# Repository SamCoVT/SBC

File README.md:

# SBC
SamCo's Single Board Computer (65C02)

This single board computer was constructed for fun.  It has the
following specifications:

* 65C02 processor
* 32K RAM (with 256 addresses reserved for I/O)
* 32K ROM 
* 65C22 Versatile Interface Adapter (VIA)
* 65C51 Asynchronous Communications Interface Adapter (ACIA)
* 2x16 LCD
* Support for USB or external 5V power

After trying out writing programs in assembly and in BASIC, I found
the [Tali Forth 2](https://github.com/scotws/TaliForth2) project, and
that's what I've been using as an operating system/programming
language ever since.

## Memory Map

The memory map is currently as follows:

|Memory Range | Function|
|-------------|--------|
|$0000-$7EFF  | RAM|
|$7F00-$7F3F  | VIA (65C22 - parallel I/O)|
|$7F40-$7F7F  | EXSEL1 (External Select #1) (Active Low)|
|$7F80-$7FBF  | ACIA (65C51 - Serial port)|
|$7FC0-$7FFF  | LCD|

The EXSEL1 line is brought out to the expansion bus on the righ
side of the PCB and is available for use.  The EXSEL2 line is an
active-high version of the /RESET signal.  Both of these signals are
not currently used by the SBC and can be repurposed by reprogramming
the GAL.

The memory decoding is handled by a GAL22V10, programmed from the
ADDECODE.PLD file.  I used Wincupl (run under Wine on Linux) to
generate the .jed (JEDEC) file, and then I used Galblast on an old
Windows 98 machine with a parallel port adapter to program the GAL.

## Errata

* Because I used a WDC65C22S (which has a totem-pole IRQ output rather
  than the WDC65C22N which has an open drain IRQ output,) I had to cut
  the IRQ trace and add a Schottky diode (cathode towards pin 21 of
  IC6) across the gap.

* I needed to add approximately 30pF of capacitance to the ACIA
  crystal to get it to start up and oscillate reliably.  No provision
  was made on the board for this, so I added it on the back side of
  the board between pins 1 and 6.  I also needed to add a 1Meg Ohm
  resistor across the crystal pins when using an RCA CDP65C51 (but did
  not need this when using a Rockwell part.)

# License
The Eagle schematic board files are provided here under a Creative
Commons BY-SA 2.0 (CC BY-SA 2.0) license.

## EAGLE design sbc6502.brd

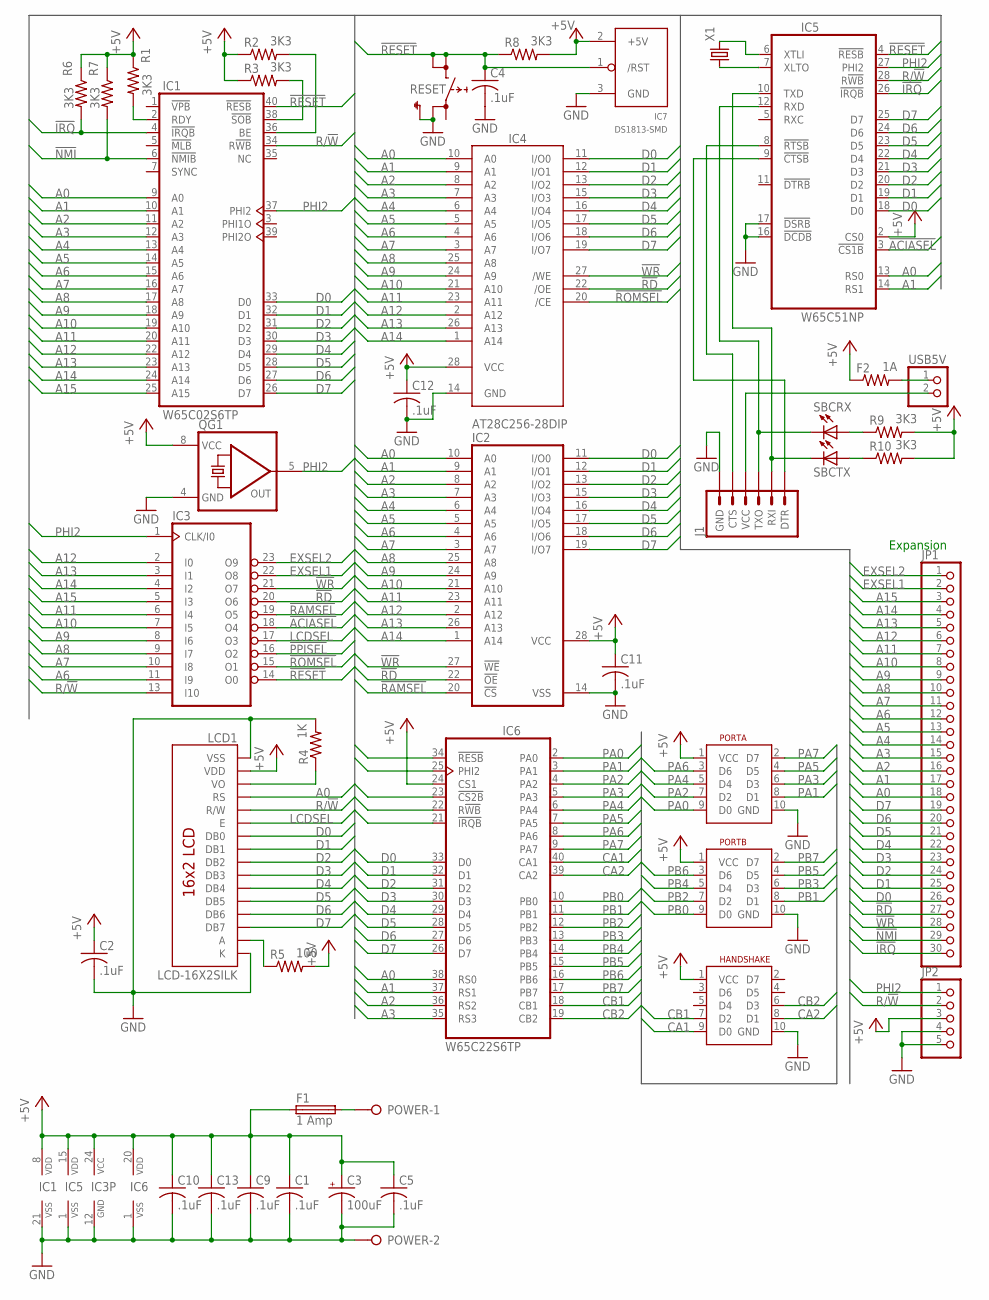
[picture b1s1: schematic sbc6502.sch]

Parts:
C1, C2, C4, C5, C9, C10, C11, C12, C13: .1uF; C0603K
C3: 100uF; E5-8,5
F1: 1 Amp; SH25
F2: 1A; R0603
HANDSHAKE: 8BIT_HEADER_SHROUDED; 2X05_SHROUDED
IC1: W65C02S6TP; DIL40
IC2: 62256P; DIL28-6
IC3: 22V10; DIL24-3
IC4: AT28C256-28DIP; DIL28-6
IC5: W65C51NP; DIL28-6
IC6: W65C22S6TP; DIL40
IC7: DS1813-SMD; SOT-23
J1: 6_PIN_SERIAL_TARGET; 1X06
JP1: PINHD-1X30; 1X30
JP2: PINHD-1X5; 1X05
LCD1: LCD-16X2SILK; LCD-16X2
PORTA: 8BIT_HEADER_SHROUDED; 2X05_SHROUDED
PORTB: 8BIT_HEADER_SHROUDED; 2X05_SHROUDED
POWER: W237-02P; W237-132
QG1: QG5460; DIL08S
R1, R2, R3, R6, R7, R8, R9, R10: 3K3; R0603
R4: 1K; R0603
R5: 100; R0805
RESET: SKHMPSE010; SKHMPXE010
SBCRX: LEDCHIPLED_0805; CHIPLED_0805
SBCTX: LEDCHIPLED_0805; CHIPLED_0805
USB5V: PINHD-1X2; 1X02
X1: CRYSTALHC49U-V; HC49U-V

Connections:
!ACIASEL: IC3.18 (O4), IC5.3 (!CS1B)
!IRQ: IC1.4 (!IRQB), IC5.26 (!IRQB), IC6.21 (!IRQB), JP1.30, R6.2
!NMI: IC1.6 (!NMIB), JP1.29, R7.2
!PPISEL: IC3.16 (O2), IC6.23 (!CS2B)
!RAMSEL: IC2.20 (!CS), IC3.19 (O5)
!RD: IC2.22 (!OE), IC3.20 (O6), IC4.22 (/OE), JP1.27
!RESET: C4.1, IC1.40 (!RESB), IC3.14 (O0), IC5.4 (!RESB), IC6.34 (!RESB), IC7.1 (/RST), R8.1, RESET.3 (2.1), RESET.4 (2.2)
!ROMSEL: IC3.15 (O1), IC4.20 (/CE)
!WR: IC2.27 (!WE), IC3.21 (O7), IC4.27 (/WE), JP1.28
+5V: C1.1, C2.1, C3.+, C5.1, C9.1, C10.1, C11.1, C12.1, C13.1, F1.1, F2.1, HANDSHAKE.1 (VCC), IC1.8 (VDD), IC2.28 (VCC), IC3.24 (VCC), IC4.28 (VCC), IC5.2 (CS0), IC5.15 (VDD), IC6.20 (VDD), IC6.24 (CS1), IC7.2 (+5V), JP2.3, LCD1.2 (VDD), PORTA.1 (VCC), PORTB.1 (VCC), QG1.8 (VCC), R1.1, R2.1, R3.1, R5.2, R6.1, R7.1, R8.2, R9.2, R10.2
A0: IC1.9 (A0), IC2.10 (A0), IC4.10 (A0), IC5.13 (RS0), IC6.38 (RS0), JP1.18, LCD1.4 (RS)
A1: IC1.10 (A1), IC2.9 (A1), IC4.9 (A1), IC5.14 (RS1), IC6.37 (RS1), JP1.17
A2: IC1.11 (A2), IC2.8 (A2), IC4.8 (A2), IC6.36 (RS2), JP1.16
A3: IC1.12 (A3), IC2.7 (A3), IC4.7 (A3), IC6.35 (RS3), JP1.15
A4: IC1.13 (A4), IC2.6 (A4), IC4.6 (A4), JP1.14
A5: IC1.14 (A5), IC2.5 (A5), IC4.5 (A5), JP1.13
A6: IC1.15 (A6), IC2.4 (A6), IC3.11 (I9), IC4.4 (A6), JP1.12
A7: IC1.16 (A7), IC2.3 (A7), IC3.10 (I8), IC4.3 (A7), JP1.11
A8: IC1.17 (A8), IC2.25 (A8), IC3.9 (I7), IC4.25 (A8), JP1.10
A9: IC1.18 (A9), IC2.24 (A9), IC3.8 (I6), IC4.24 (A9), JP1.9
A10: IC1.19 (A10), IC2.21 (A10), IC3.7 (I5), IC4.21 (A10), JP1.8
A11: IC1.20 (A11), IC2.23 (A11), IC3.6 (I4), IC4.23 (A11), JP1.7
A12: IC1.22 (A12), IC2.2 (A12), IC3.2 (I0), IC4.2 (A12), JP1.6
A13: IC1.23 (A13), IC2.26 (A13), IC3.3 (I1), IC4.26 (A13), JP1.5
A14: IC1.24 (A14), IC2.1 (A14), IC3.4 (I2), IC4.1 (A14), JP1.4
A15: IC1.25 (A15), IC3.5 (I3), JP1.3
CA1: HANDSHAKE.9 (D0), IC6.40 (CA1)
CA2: HANDSHAKE.8 (D1), IC6.39 (CA2)
CB1: HANDSHAKE.7 (D2), IC6.18 (CB1)
CB2: HANDSHAKE.6 (D3), IC6.19 (CB2)
D0: IC1.33 (D0), IC2.11 (I/O0), IC4.11 (I/O0), IC5.18 (D0), IC6.33 (D0), JP1.26, LCD1.7 (DB0)
D1: IC1.32 (D1), IC2.12 (I/O1), IC4.12 (I/O1), IC5.19 (D1), IC6.32 (D1), JP1.25, LCD1.8 (DB1)
D2: IC1.31 (D2), IC2.13 (I/O2), IC4.13 (I/O2), IC5.20 (D2), IC6.31 (D2), JP1.24, LCD1.9 (DB2)
D3: IC1.30 (D3), IC2.15 (I/O3), IC4.15 (I/O3), IC5.21 (D3), IC6.30 (D3), JP1.23, LCD1.10 (DB3)
D4: IC1.29 (D4), IC2.16 (I/O4), IC4.16 (I/O4), IC5.22 (D4), IC6.29 (D4), JP1.22, LCD1.11 (DB4)
D5: IC1.28 (D5), IC2.17 (I/O5), IC4.17 (I/O5), IC5.23 (D5), IC6.28 (D5), JP1.21, LCD1.12 (DB5)
D6: IC1.27 (D6), IC2.18 (I/O6), IC4.18 (I/O6), IC5.24 (D6), IC6.27 (D6), JP1.20, LCD1.13 (DB6)
D7: IC1.26 (D7), IC2.19 (I/O7), IC4.19 (I/O7), IC5.25 (D7), IC6.26 (D7), JP1.19, LCD1.14 (DB7)
EXSEL1: IC3.22 (O8), JP1.2
EXSEL2: IC3.23 (O9), JP1.1
GND: C1.2, C2.2, C3.-, C4.2, C5.2, C9.2, C10.2, C11.2, C12.2, C13.2, HANDSHAKE.10 (GND), IC1.21 (VSS), IC2.14 (VSS), IC3.12 (GND), IC4.14 (GND), IC5.1 (VSS), IC5.16 (!DCDB), IC5.17 (!DSRB), IC6.1 (VSS), IC7.3 (GND), J1.6 (GND), JP2.4, JP2.5, LCD1.1 (VSS), LCD1.16 (K), PORTA.10 (GND), PORTB.10 (GND), POWER.2, QG1.4 (GND), R4.2, RESET.2 (1.2), RESET.5 (SH)
LCDSEL: IC3.17 (O3), LCD1.6 (E)
unnamed: LCD1.15 (A), R5.1
unnamed: LCD1.3 (VO), R4.1
unnamed: R9.1, SBCRX.A
unnamed: R10.1, SBCTX.A
unnamed: IC1.2 (RDY), R1.2
unnamed: IC1.38 (!SOB), R3.2
unnamed: IC1.36 (BE), R2.2
unnamed: IC5.7 (XLTO), X1.1
unnamed: IC5.6 (XTLI), X1.2
unnamed: J1.4 (VCC), USB5V.2
unnamed: F1.2, POWER.1
unnamed: F2.2, USB5V.1
PA0: IC6.2 (PA0), PORTA.9 (D0)
PA1: IC6.3 (PA1), PORTA.8 (D1)
PA2: IC6.4 (PA2), PORTA.7 (D2)
PA3: IC6.5 (PA3), PORTA.6 (D3)
PA4: IC6.6 (PA4), PORTA.5 (D4)
PA5: IC6.7 (PA5), PORTA.4 (D5)
PA6: IC6.8 (PA6), PORTA.3 (D6)
PA7: IC6.9 (PA7), PORTA.2 (D7)
PB0: IC6.10 (PB0), PORTB.9 (D0)
PB1: IC6.11 (PB1), PORTB.8 (D1)
PB2: IC6.12 (PB2), PORTB.7 (D2)
PB3: IC6.13 (PB3), PORTB.6 (D3)
PB4: IC6.14 (PB4), PORTB.5 (D4)
PB5: IC6.15 (PB5), PORTB.4 (D5)
PB6: IC6.16 (PB6), PORTB.3 (D6)
PB7: IC6.17 (PB7), PORTB.2 (D7)
PHI2: IC1.37 (PHI2), IC3.1 (CLK/I0), IC5.27 (PHI2), IC6.25 (PHI2), JP2.1, QG1.5 (OUT)
R/!W!: IC1.34 (R!WB), IC3.13 (I10), IC5.28 (R!WB), IC6.22 (R!WB), JP2.2, LCD1.5 (R/W)
SBCRX: IC5.12 (RXD), J1.3 (TXO), SBCRX.C
SBC_CTS: IC5.9 (!CTSB), J1.1 (DTR)
SBC_RTS: IC5.8 (!RTSB), J1.5 (CTS)
SBC_TX: IC5.10 (TXD), J1.2 (RXI), SBCTX.C

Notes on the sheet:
Expansion

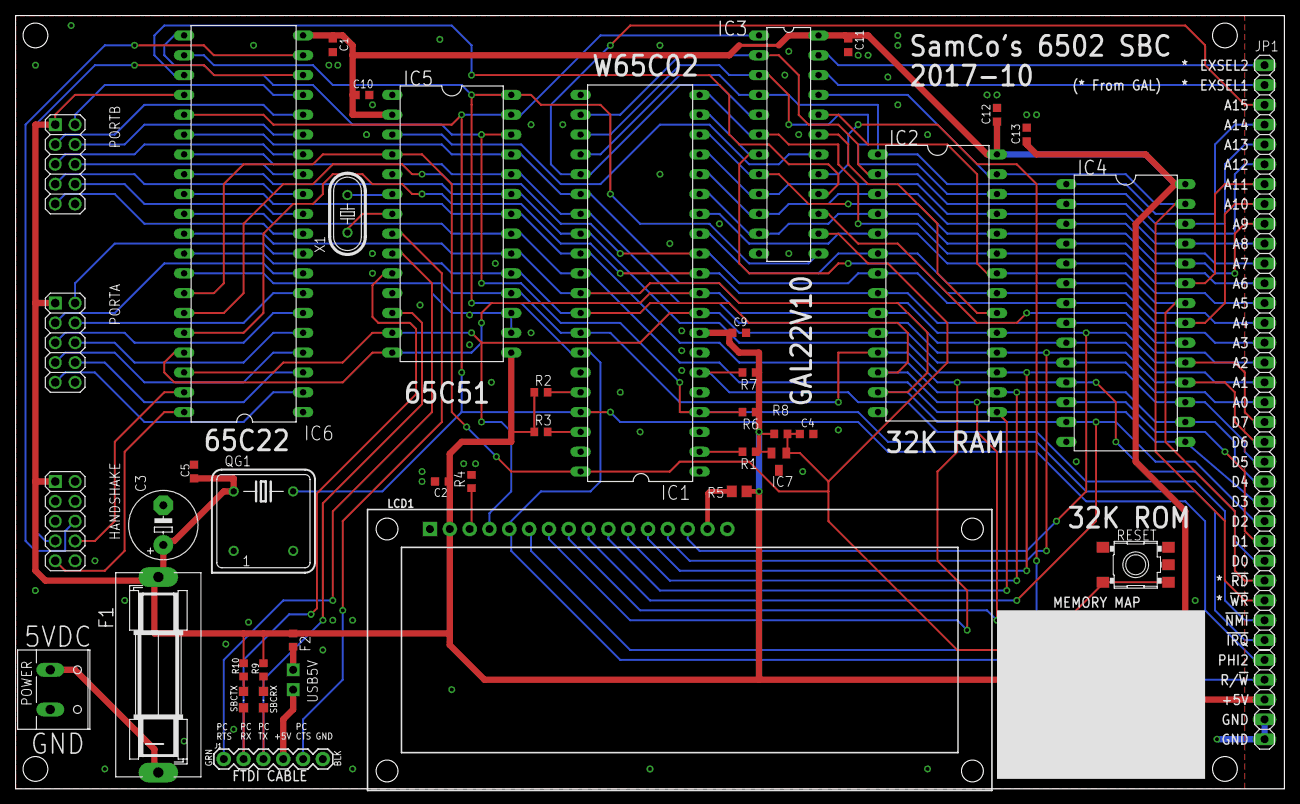
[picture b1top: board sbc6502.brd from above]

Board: 2 copper layers, 162.6 x 99.1 mm, 43 parts (0 on the bottom side), 76 nets.

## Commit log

2018-10-30 Initial files for SBC
2018-10-31 Adding schematic as a PNG image
2018-11-18 I2C routines for Tali Forth 2
    These should be added to the user words to handle a 24FC1025 128K EEPROM on PORTA of the VIA.
    SDA (Serial DAta) is on PORTA Bit 7
    SCL (Serial CLock) is on PORTA Bit 0
2018-11-18 Address Decoder GAL files
    I'm using a GAL22V10, programmed with GALBLAST via the parallel port on an old Win98 machine.
    The PIT (Programmable Interval Timer) mentioned in the ADDECODE.PLD file was never used, and that output (connected to EXSEL1 on the PCB) is available as an active low select line for the addresses $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
2018-11-18 Update i2c.fs
    Switch back to decimal at the end.
2018-11-29 Update i2c.fs
    Remove comment mentioning the need to load blocks.fs first, as Tali2 already has these words now.
2018-11-30 Add GAL information and address map
    Adding address map and how GAL was programmed.
2018-12-09 Update i2c for vectored block I/O
    When assemblerizing the block words, the `BLOCK-READ` and `BLOCK-WRITE` words changed from deferred words (which don't work in ROM) to vectored words using `BLOCK-READ-VECTOR` and `BLOCK-WRITE-VECTOR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

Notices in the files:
parts and their libraries:
SparkFun-Displays: Licensing: Creative Commons ShareAlike 4.0 International - https://creativecommons.org/licenses/by-sa/4.0
